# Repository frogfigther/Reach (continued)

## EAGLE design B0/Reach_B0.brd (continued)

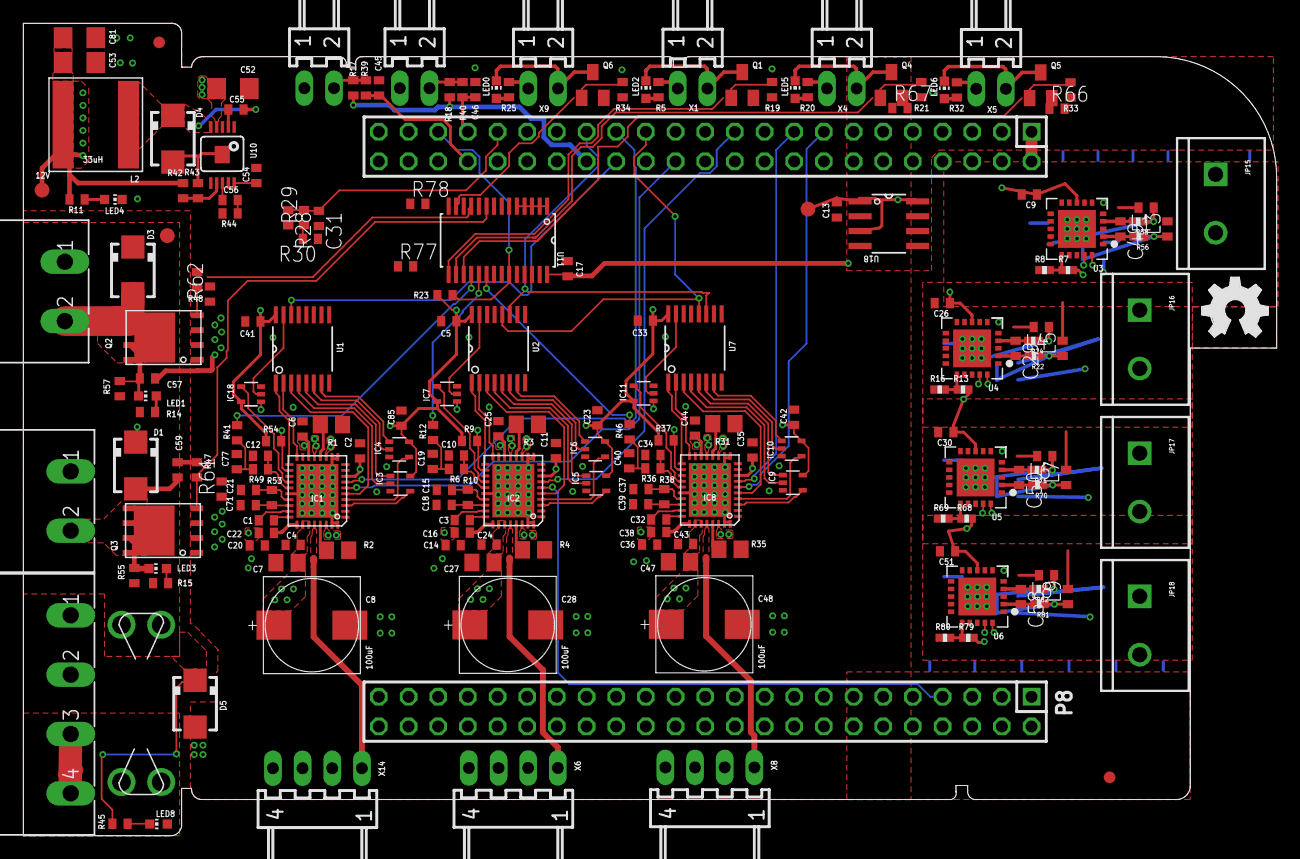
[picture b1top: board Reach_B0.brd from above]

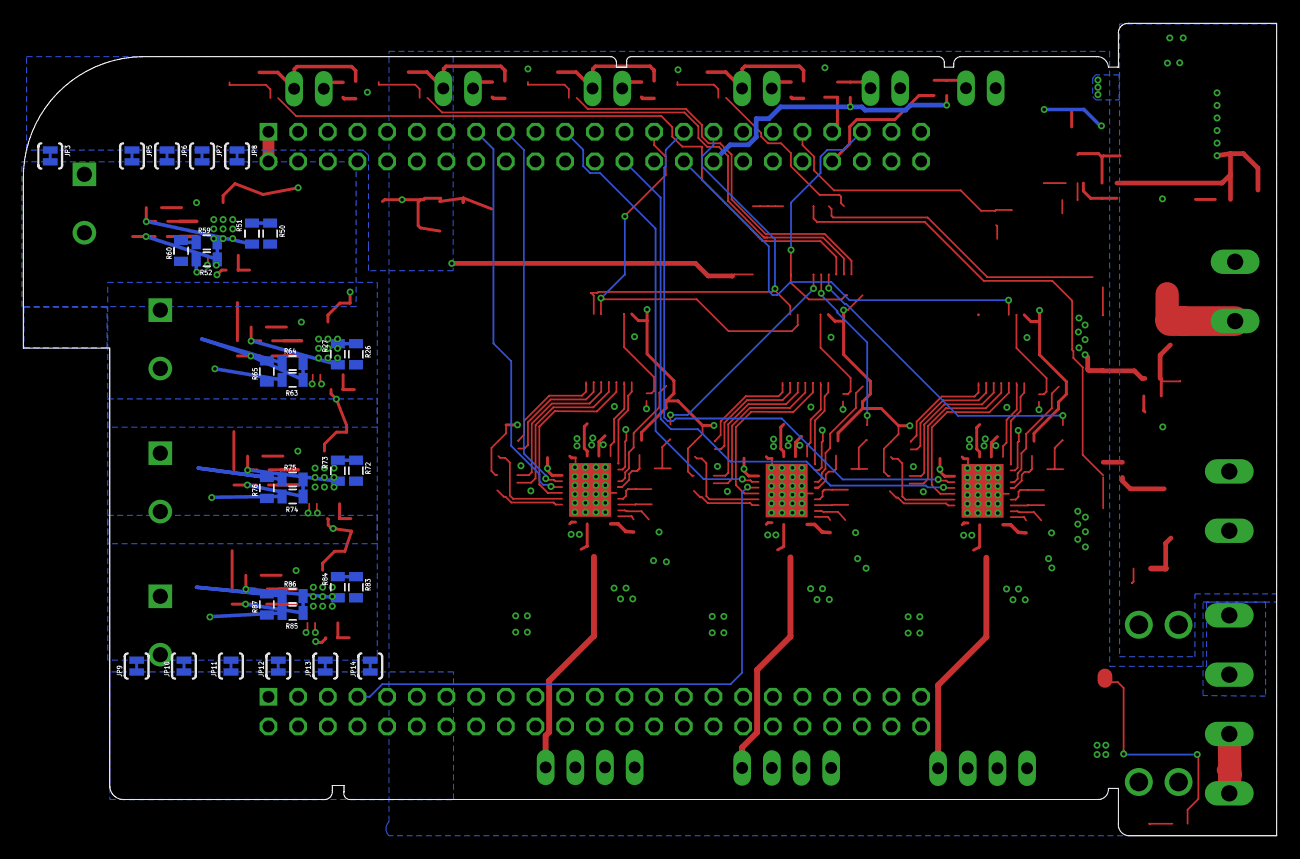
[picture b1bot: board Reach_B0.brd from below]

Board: 4 copper layers, 107.3 x 69.5 mm, 237 parts (31 on the bottom side), 173 nets.

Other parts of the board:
U$1: LOGO_BIG

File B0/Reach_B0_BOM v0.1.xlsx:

Qty | Value | Device | Package | Parts | Description | Digikey | Qty 1 | Qty 10 | Qty 100 | Qty 500 | Qty 1000/5000 | Board Qty 1 |  | Board Qty 100 |  | Board Qty 500
6 | 22-05-7028-02 | 22-05-7028-02 | 7395-02 | X1, X4, X5, X7, X9, X11 | CONNECTOR | A19450-ND | 0.1 | 0.81 | 5.01 | 20.73 | 82.04 | 0.60000000000000009 |  | 24.876000000000001 |  | 15.03
3 | 22-05-7048-04 | 22-05-7048-04 | 7395-04 | X6, X8, X14 | CONNECTOR | A19452-ND | 0.16 | 1.54 | 9.5 | 39.299999999999997 | 68.78 | 0.48 |  | 28.5 |  | 14.25
9 | 74AHC1G126DCK | 74AHC1G126DCK | SC70-5 | IC3, IC4, IC5, IC6, IC7, IC9, IC10, IC11, IC18 | Single Bus Buffer Gate With 3-State Outputs | 296-8747-1-ND | 0.42 | 3.14 | 19.57 | 66.95 | 103 | 3.14 | Qty 10 | 120.51000000000002 |  | 88.064999999999998
2 | AON6752 | AON6752 | 8-DFN-EP-(5X6) | Q2, Q3 |  | 785-1498-1-ND | 1.1299999999999999 | 9.9700000000000006 | 78.83 | 305.68 | 482.66 | 2.2599999999999998 |  | 157.66 |  | 78.83
8 | BLM15HB121SN1 | BLM15HB121SN1 | 402 | L1, L3, L4, L5, L6, L7, L8, L9 | EMIFIL (R) Chip Ferrite Bead for GHz Noise | 490-4000-1-ND | 0.19 | 1.45 | 9.33 | 35.25 | 60.13 | 1.45 | Qty 10 | 56.399999999999991 |  | 240.52
3 | 100uF | C | RHS1V10MCN1GS | C8, C28, C48 |  | PCE4238CT-ND | 0.52 | 3.59 | 21.52 |  |  | 1.56 |  | 64.56 |  | 213.31 | PCE4238TR-ND Tape and Reel
34 | 0.1uF | C-EUC0402 | C0402 | C2, C5, C9, C11, C13, C14, C16, C17, C18, C20, C22, C23, C26, C29, C30, C33, C3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 | CAPACITOR, European symbol | 445-12185-1-ND | 0.15 | 1.05 | 4.95 | 17.36 | 122.39 | 3.57 | Qty 10 Break | 118.048 |  | 416.12599999999998
2 | 10nF | C-EUC0402 | C0402 | C54, C55 | CAPACITOR, European symbol | 445-12173-1-ND | 0.1 | 0.36 | 1.61 | 5.76 | 9.0399999999999991 | 0.2 |  | 3.2199999999999998 |  | 9.0399999999999991
1 | 1nF | C-EUC0402 | C0402 | C56 | CAPACITOR, European symbol | 490-6315-1-ND | 0.1 | 0.26 | 1.18 | 4.22 |  | 0.1 |  | 1.18 |  | 4.22
3 | 22nF | C-EUC0402 | C0402 | C1, C3, C32 | CAPACITOR, European symbol | 490-8256-1-ND | 0.1 | 0.26 | 1.18 | 4.22 |  | 0.26 | Qty 10 | 3.54 |  | 12.66
14 | 4.7uF | C-EUC0402 | C0402 | C10, C12, C15, C19, C21, C31, C34, C37, C40, C77, C57, C59, C45, C46 | CAPACITOR, European symbol | 490-5915-1-ND | 0.49 | 3.41 | 20.46 | 76.709999999999994 | 129.25 | 4.774 | Qty 10 Break | 214.78800000000001 |  | 180.95000000000002
6 | 10uF | C-EUC0805 | C0805 | C7, C27, C47, C52, C53, C81 | CAPACITOR, European symbol | 587-3489-1-ND | 0.31 | 2.12 | 12 | 42.36 |  | 1.8599999999999999 |  | 50.832000000000001 |  | 254.16000000000003
1 | CAT24C256 | CAT24C256 | SOIC127P600X175-8N | U18 |  | CAT24C256WI-GT3OSCT-ND | 0.4 | 3.89 | 31.93 | 155.21 |  | 0.4 |  | 31.929999999999996 |  | 155.21
2 | F-2X23- | F-2X23- | DIL-100-2X23 | P8, P9 |  | SAM1204-23-ND | 4.95 | 44.28 | 364.68 | 1441.36 | 2474.63 | 9.9 |  | 729.36 |  | 2474.63
1 | FUSE | FUSE | F4991-ND | F1 | Fuse | F4991-ND | 0.37 | 3.47 | 24.2 | 93.5 |  | 0.37 |  | 24.2 |  | 93.5
2 | FUSE | FUSE | 3557 | F1 | Fuse | 36-3557-ND | 0.21 | 1.97 | 13.68 | 57.86 | 94.68 | 0.42 |  | 27.36 |  | 94.68
8 | blue | LEDCHIP-LED0603 | CHIP-LED0603 | LED1, LED3, LED8, LED0, LED2, LED4, LED5, LED6 | LED | 475-2816-1-ND | 0.34 | 2.4 | 15.97 | 47.92 | 79.86 | 2.4 | Qty 10 | 76.672000000000011 |  | 319.44
1 |  | M025MM | SCREWTERMINAL-5MM-2 | JP15 | Header 2 | 277-1667-ND | 0.39 | 3.75 | 34.92 | 150.13999999999999 |  | 0.39 |  | 34.92 |  | 150.13999999999999
4 | MBRA340T3 | MBRA340T3 | SMA | D1, D3, D4, D5 | Surface Mount Schottky Power Rectifier | MBRA340T3GOSCT-ND | 0.47 | 4.0199999999999996 | 29.98 | 117.78 | 182.03 | 1.88 |  | 117.78 | Qty 500 | 364.06
4 | MCP9600 | MCP9600 | MQFN-20 | U3, U4, U5, U6 |  | MCP9600-I/MX-ND | 5.04 |  | 382.13 |  |  | 20.16 |  | 1528.52 |  | 7642.5999999999995
2 | MSTBA2 | MSTBA2 | MSTBA2 | X3, X21 | PHOENIX | 277-1106-ND | 0.6 | 5.75 | 53.48 | 229.91 | 416.5 | 1.2 |  | 106.96 |  | 416.5
1 | MSTBA4 | MSTBA4 | MSTBA4 | X2 | PHOENIX | 277-7452-ND | 1.3 | 12.63 | 108.56 | 477.9 |  | 1.3 |  | 108.56000000000002 |  | 477.9
3 | NEWPORT_THERMOCOUPLE_CONNECTORPCC-SMP-V | NEWPORT_THERMOCOUPLE_CONNECTORPCC-SMP-V | PCC-SMP-V | XTC2, XTC3, XTC4 | Newport Electronics miniature Thermocouple connector. | PCC-SMP-V-K | 2.2000000000000002 |  |  |  | Newark Only | 6.6000000000000005 |  | 660 |  | 3300.0000000000005
4 |  | NPN-TRANSISTOR_SOT23 | SOT23 | Q1, Q4, Q5, Q6 | NPN TRANSISTOR | MMBT2222ALT1GOSCT-ND | 0.11 | 1.01 | 5.52 | 16.989999999999998 | 23.17 | 0.44 |  | 16.989999999999998 | Qty 500 | 46.34
1 | PCA9685PW | PCA9685PW | SOP65P640X110-28N | U11 | 16-channel, 12-bit PWM Fm+ I2C-bus LED controller | 568-5931-1-ND | 2.4300000000000002 | 21.84 | 175.51 | 721 |  | 2.4300000000000002 |  | 175.51 |  | 721
13 | 10K | R-EU_R0402 | R0402 | R6, R12, R36, R41, R46, R49, R39, R40, R43, R28, R13, R68, R79 | RESISTOR, European symbol | RMCF0402FT10K0CT-ND | 0.1 | 0.2 | 0.81 | 3.64 | 13.06 | 1.3 |  | 9.4640000000000004 |  | 16.978000000000002
1 | 120K,1% | R-EU_R0402 | R0402 | R42 | RESISTOR, European symbol | RMCF0402FT120KCT-ND | 0.1 | 0.2 | 0.81 | 3.64 |  | 0.1 |  | 0.81000000000000016 |  | 3.64
3 | 2.2R | R-EU_R0402 | R0402 | R10, R38, R53 | RESISTOR, European symbol | RMCF0402FT2R20CT-ND | 0.1 | 0.21 | 0.86 |  | 3.85 | 0.30000000000000004 |  | 2.58 |  | 5.7750000000000004
1 | 39K | R-EU_R0402 | R0402 | R44 | RESISTOR, European symbol | RMCF0402FT39K0CT-ND | 0.1 | 0.2 | 0.81 |  | 3.64 | 0.1 |  | 0.81000000000000016 |  | 3.64 | Qty 1000
2 | 4.3k | R-EU_R0402 | R0402 | R30, R69 | RESISTOR, European symbol | RMCF0402FT4K30CT-ND | 0.1 | 0.2 | 0.81 |  | 3.64 | 0.2 |  | 1.6200000000000003 |  | 3.64
22 | 4.7K | R-EU_R0402 | R0402 | R9, R14, R15, R23, R37, R45, R47, R48, R54, R55, R57, R5, R11, R19, R20, R21, R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 | RESISTOR, European symbol | RMCF0402FT4K70CT-ND | 0.1 | 0.2 | 0.81 |  | 13.06 | 0.44000000000000006 | Qty 10 Break | 57.463999999999999 |  | 28.732000000000003
2 | 7.5k | R-EU_R0402 | R0402 | R29 | RESISTOR, European symbol | RMCF0402FT7K50CT-ND | 0.1 | 0.2 | 0.81 |  | 3.64 | 0.2 | Qty 10 | 1.6200000000000003 |  | 3.64
6 | 0.1R | R-EU_R0805 | R0805 | R1, R2, R3, R4, R31, R35 | RESISTOR, European symbol | RMCF0805JTR100CT-ND | 0.44 | 3.18 | 12.73 |  | 145.31 | 2.64 |  | 76.38 |  | 174.37200000000001
1 | 0 | RESISTOR0402-RES | R0402 | R8 | Resistor | 311-0.0JRCT-ND | 0.1 | 0.1 | 0.38 | 1.1499999999999999 |  | 0.1 |  | 0.38 |  | 1.1499999999999999
8 | 100 | RESISTOR0402-RES | R0402 | R22, R24, R56, R58, R70, R71, R81, R82 | Resistor | RMCF0402FT100RCT-ND | 0.1 | 0.2 | 0.81 | 3.64 | 7.91 | 0.2 | Qty 10 | 3.64 | Qty 500 | 13.05 | Qty 5000
1 | 2.2k | RESISTOR0402-RES | R0402 | R16 | Resistor | RMCF0402FT2K20CT-ND | 0.1 | 0.2 | 0.81 | 3.64 |  | 0.1 |  | 0.81000000000000016 |  | 3.64
6 | 0 | RESISTOR0805-RES | R0805 | R66, R67, R77, R78, R88, R89 | Resistor | RMCF0805ZT0R00CT-ND | 0.1 | 0.16 | 0.65 | 1.98 | 2.92 | 0.16 | Qty 10 | 2.3759999999999999 |  | 8.76
20 | 10k | RESISTOR0805-RES | R0805 | R26, R27, R50, R51, R52, R59, R60, R63, R64, R65, R72, R73, R74, R75, R76, R83,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 | Resistor | RMCF0805FT10K0CT-ND | 0.1 | 0.23 | 0.95 |  |  | 0.46 | Qty 10 Break | 19 |  | 26.5 | RMCF0805FT10K0TR-ND
1 | 33uH | RT8040T330 | NR8040T330 | L2 |  | 587-2636-1-ND | 0.62 | 5.43 | 38.81 | 163.01 |  | 0.62 |  | 38.81 |  | 163.01
1 | RT8268 | RT8268 | MSOP10 | U10 |  | 1028-1045-1-ND | 0.74 | 6.49 | 50.06 | 185.4 |  | 0.74 |  | 50.06 |  | 185.4
3 | SN74AHC595PW | SN74AHC595PW | SOP65P640X120-16N | U1, U2, U7 | 8 bit shift registers with 3-state output registers | 296-4620-1-ND | 0.54 | 4.6399999999999997 | 34.61 | 135.96 | 210.12 | 1.62 |  | 103.83000000000001 |  | 315.18
3 | TMC2130QFN36 | TMC2130QFN36 | QFN36 | IC1, IC2, IC8 |  | 1460-1130-1-ND | 5.33 | 47.58 | 390.16 | 1579.66 |  | 15.99 |  | 1170.48 |  | 4738.9800000000005
 |  |  |  |  |  |  |  |  |  |  | Totals | 93.413999999999973 |  | 6023.010000000002 |  | 23479.247999999996
 |  |  |  |  |  |  |  |  |  |  | Cost Per Board | 93.413999999999973 |  | 60.230100000000022 |  | 46.95849599999999

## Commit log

2017-03-10 added pinout files and a basic BOM
2017-03-10 Create .gitignore
    basic ignore list
2017-03-10 Create B0
2017-03-10 reach version B0 for replicape
    Nightly upload of reach board for replicape 3/10/17
2017-03-11 I2C address tally
2017-03-11 multisheet schematic changes
2017-03-12 stepper drivers laid out
2017-03-12 example layout of esd and low pass filter added to thermocouple1
2017-03-13 added credit to Elias
2017-03-13 supply layout complete
2017-03-18 thermocouple layout complete
2017-03-19 FETs added
2017-03-20 added combined pinout of reach and replicape
    still needs a lot of work
2017-03-30 reformat of document layout
2017-03-30 CC-BY-SA4.0
    since the original reach files are published under CC-BY-SA we are required to do the same
2017-04-16 update pin map
2017-05-08 Add files via upload
    Changed pinout to make layout simpler
2017-07-30 TMC2130
    Updated to TMC2130 for stepper driver, testing screw terminal layout for thermocouple connections (thermocouple connectors too expensive).
2017-07-30 Added Naming Conventions
2017-11-29 Shortened the link to the source repo
    Original link was way longer than practical
    (https://bitbucket.org/intelligentagent/replicape/src/2717a4b54c66b592cc67d7cf700adc2b5288bc23/Reach_rev_B0/?at=master)
2017-11-29 removed LCD jumpers
